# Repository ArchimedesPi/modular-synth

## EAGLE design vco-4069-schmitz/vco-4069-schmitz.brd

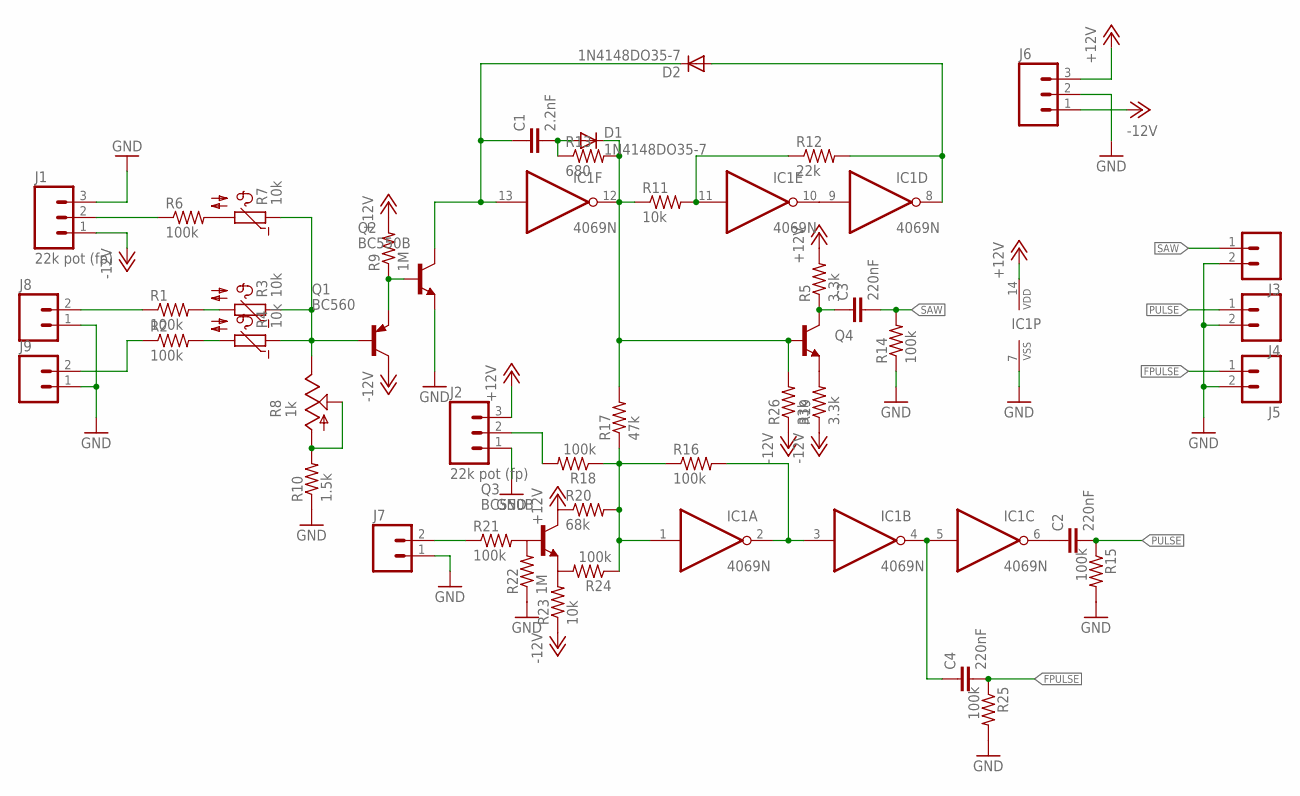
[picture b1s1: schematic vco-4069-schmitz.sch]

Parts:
C1: 2.2nF; C025-025X050
C2, C3, C4: 220nF; C025-025X050
D1, D2: 1N4148DO35-7; DO35-7
IC1: 4069N; DIL14
J1, J2: 22k pot (fp); 1X03
J3, J4, J5, J7, J8, J9: M02PTH; 1X02
J6: M03PTH; 1X03
Q1: BC560; TO92-EBC
Q2, Q3: BC550B; TO92-EBC
Q4: TRANSISTOR_NPNBC547; TO-92-AMMO
R1, R2, R6, R14, R15, R16, R18, R21, R24, R25: 100k; 0207/2V
R3, R4, R7: 10k; N640
R5, R19: 3.3k; 0207/2V
R8: 1k; B25P
R9, R22: 1M; 0207/2V
R10: 1.5k; 0207/2V
R11: 10k; 0207/2V
R12: 22k; 0207/2V
R13: 680; 0204/7
R17: 47k; 0207/2V
R20: 68k; 0207/2V
R23: 10k; 0207/5V
R26: 33k; 0207/2V

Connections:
+12V: IC1.14 (VDD), J2.3, J6.3, Q3.C, R5.2, R9.2, R20.1
-12V: J1.1, J6.1, Q1.C, R19.1, R23.1, R26.1
CV2: J9.2, R2.1
FPULSE: C4.2, J5.1, R25.1
GND: IC1.7 (VSS), J1.3, J2.1, J3.2, J4.2, J5.2, J6.2, J7.1, J8.1, J9.1, Q2.E, R10.1, R14.1, R15.2, R22.1, R25.2
unnamed: J1.2, R6.1
unnamed: R1.2, R3.2
unnamed: R6.2, R7.2
unnamed: R2.2, R4.2
unnamed: Q3.E, R23.2, R24.2
unnamed: Q1.E, Q2.B, R9.1
unnamed: R8.A, R8.S, R10.2
unnamed: C1.1, D2.C, IC1.13 (I), Q2.C
unnamed: IC1.2 (O), IC1.3 (I), R16.2
unnamed: IC1.11 (I), R11.2, R12.1
unnamed: IC1.9 (I), IC1.10 (O)
unnamed: D2.A, IC1.8 (O), R12.2
unnamed: C1.2, D1.A, R13.1
unnamed: Q4.3 (E), R19.2
unnamed: C4.1, IC1.4 (O), IC1.5 (I)
unnamed: C2.1, IC1.6 (O)
unnamed: IC1.1 (I), R16.1, R17.1, R18.1, R20.2, R24.1
unnamed: J2.2, R18.2
unnamed: Q3.B, R21.2, R22.2
unnamed: Q1.B, R3.1, R4.1, R7.1, R8.E
unnamed: J7.2, R21.1
unnamed: J8.2, R1.1
unnamed: C3.1, Q4.1 (C), R5.1
unnamed: D1.C, IC1.12 (O), Q4.2 (B), R11.1, R13.2, R17.2, R26.2
PULSE: C2.2, J4.1, R15.1
SAW: C3.2, J3.1, R14.2

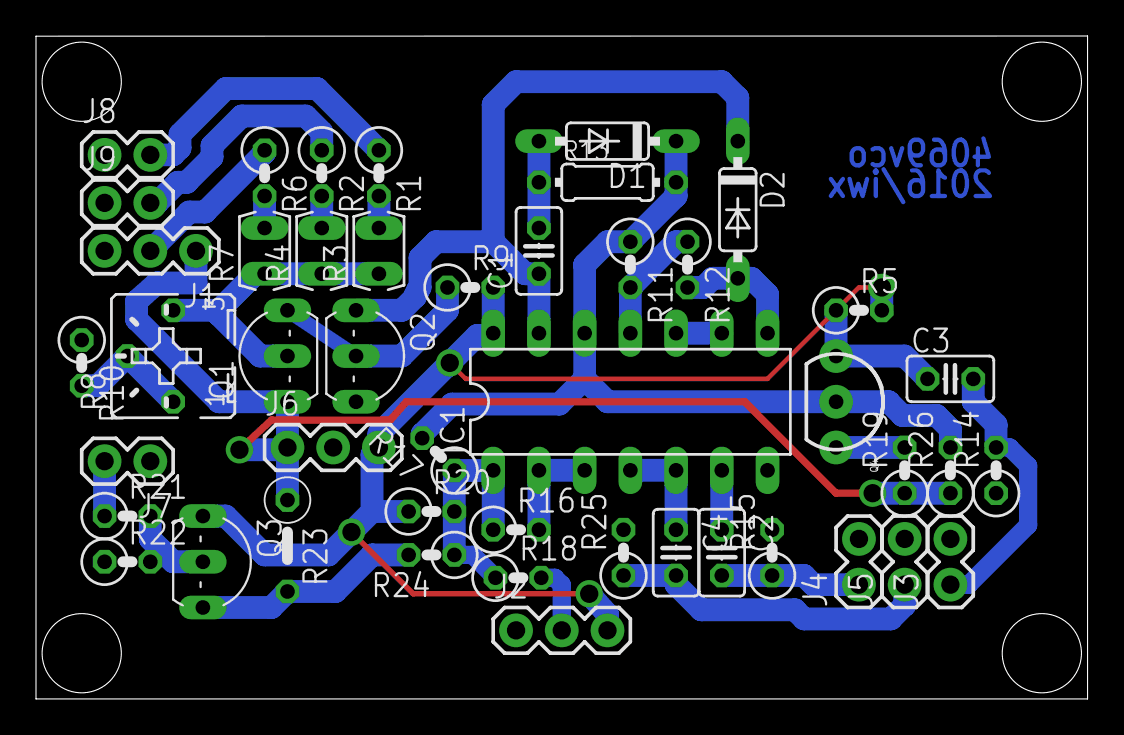
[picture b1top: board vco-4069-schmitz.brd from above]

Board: 2 copper layers, 58.4 x 36.8 mm, 46 parts (0 on the bottom side), 31 nets.

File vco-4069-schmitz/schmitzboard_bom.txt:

Partlist

Exported from vco-4069-schmitz.brd at 7/19/16 8:29 PM

EAGLE Version 7.6.0 Copyright (c) 1988-2016 CadSoft

Assembly variant: 

Part     Value          Package      Library               Position (inch)       Orientation

C1       2.2nF          C025-025X050 resistor              (1.1 0.98)            R90
C2       220nF          C025-025X050 resistor              (1.5 0.32)            R270
C3       220nF          C025-025X050 resistor              (2 0.7)               R0
C4       220nF          C025-025X050 resistor              (1.4 0.32)            R270
D1       1N4148DO35-7   DO35-7       diode                 (1.25 1.22)           R180
D2       1N4148DO35-7   DO35-7       diode                 (1.535 1.07)          R270
IC1      4069N          DIL14        40xx                  (1.3 0.65)            R0
J1       22k pot (fp)   1X03         SparkFun-Connectors   (0.35 0.98)           R180
J2       22k pot (fp)   1X03         SparkFun-Connectors   (1.05 0.15)           R0
J3                      1X02         SparkFun-Connectors   (2 0.25)              R90
J4                      1X02         SparkFun-Connectors   (1.8 0.25)            R90
J5                      1X02         SparkFun-Connectors   (1.9 0.25)            R90
J6                      1X03         SparkFun-Connectors   (0.55 0.55)           R0
J7                      1X02         SparkFun-Connectors   (0.25 0.52)           R180
J8                      1X02         SparkFun-Connectors   (0.15 1.19)           R0
J9                      1X02         SparkFun-Connectors   (0.15 1.085)          R0
Q1       BC560          TO92-EBC     transistor-pnp        (0.5 0.75)            R90
Q2       BC550B         TO92-EBC     transistor-npn        (0.75 0.75)           R270
Q3       BC550B         TO92-EBC     transistor-npn        (0.415 0.3)           R270
Q4                      TO-92-AMMO   SparkFun-DiscreteSemi (1.75 0.65)           R270
R1       100k           0207/2V      resistor              (0.75 1.15)           R270
R2       100k           0207/2V      resistor              (0.625 1.15)          R270
R3       10k            N640         ptc-ntc               (0.75 0.98)           R90
R4       10k            N640         ptc-ntc               (0.625 0.98)          R90
R5       3.3k           0207/2V      resistor              (1.8 0.85)            R0
R6       100k           0207/2V      resistor              (0.5 1.15)            R270
R7       10k            N640         ptc-ntc               (0.5 0.98)            R90
R8       1k             B25P         pot                   (0.3 0.75)            R90
R9       1M             0207/2V      resistor              (0.95 0.9)            R0
R10      1.5k           0207/2V      resistor              (0.1 0.735)           R270
R11      10k            0207/2V      resistor              (1.3 0.95)            R270
R12      22k            0207/2V      resistor              (1.425 0.95)          R270
R13      680            0204/7       resistor              (1.25 1.13)           R0
R14      100k           0207/2V      resistor              (2.1 0.5)             R90
R15      100k           0207/2V      resistor              (1.61 0.32)           R90
R16      100k           0207/2V      resistor              (1.05 0.37)           R0
R17      47k            0207/2V      resistor              (0.88 0.535)          R135
R18      100k           0207/2V      resistor              (1.055 0.265)         R0
R19      3.3k           0207/2V      resistor              (1.9 0.5)             R90
R20      68k            0207/2V      resistor              (0.865 0.41)          R0
R21      100k           0207/2V      resistor              (0.2 0.4)             R0
R22      1M             0207/2V      resistor              (0.2 0.3)             R0
R23      10k            0207/5V      resistor              (0.55 0.335)          R270
R24      100k           0207/2V      resistor              (0.865 0.315)         R180
R25      100k           0207/2V      resistor              (1.285 0.32)          R90
R26      33k            0207/2V      resistor              (2 0.5)               R90

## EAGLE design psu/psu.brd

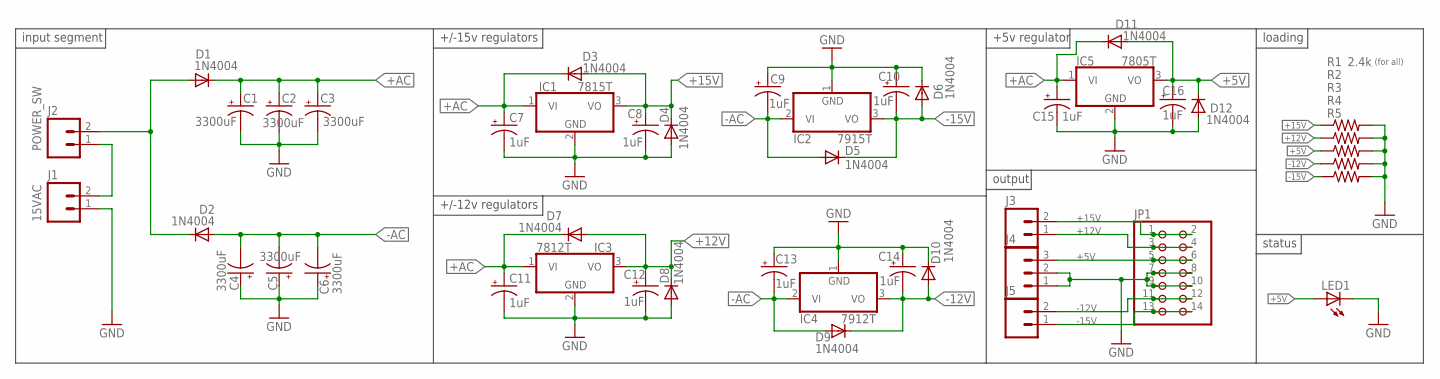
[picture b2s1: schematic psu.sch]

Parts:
C1, C2, C3, C4, C5, C6: 3300uF; E7,5-18
C7, C8, C9, C10, C11, C12, C13, C14, C15, C16: 1uF; E2,5-5
D1, D2, D3, D4, D5, D6, D7, D8, D9, D10, D11, D12: 1N4004; DO41-10
IC1: 7815T; TO220H
IC2: 7915T; TO220H
IC3: 7812T; TO220H
IC4: 7912T; TO220H
IC5: 7805T; TO220H
J1: 15VAC; SCREWTERMINAL-5MM-2
J2: POWER_SW; SCREWTERMINAL-5MM-2
J3, J5: M025MM; SCREWTERMINAL-5MM-2
J4: M03-SCREW-5MM; SCREWTERMINAL-5MM-3
JP1: PINHD-2X7; 2X07
LED1: LED3MM
R1, R2, R3, R4, R5: 2.4k; 0805

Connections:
+5V: C16.+, D11.A, D12.C, IC5.3 (VO), J4.3, JP1.5, JP1.6, LED1.A, R3.1
+12V: C12.+, D7.A, D8.C, IC3.3 (VO), J3.1, JP1.3, JP1.4, R2.1
+15V: C8.+, D3.A, D4.C, IC1.3 (VO), J3.2, JP1.1, JP1.2, R1.1
+AC: C1.+, C2.+, C3.+, C7.+, C11.+, C15.+, D1.C, D3.C, D7.C, D11.C, IC1.1 (VI), IC3.1 (VI), IC5.1 (VI)
-12V: C14.-, D9.C, D10.A, IC4.3 (VO), J5.2, JP1.11, JP1.12, R4.1
-15V: C10.-, D5.C, D6.A, IC2.3 (VO), J5.1, JP1.13, JP1.14, R5.1
-AC: C4.-, C5.-, C6.-, C9.-, C13.-, D2.A, D5.A, D9.A, IC2.2 (VI), IC4.2 (VI)
GND: C1.-, C2.-, C3.-, C4.+, C5.+, C6.+, C7.-, C8.-, C9.+, C10.+, C11.-, C12.-, C13.+, C14.+, C15.-, C16.-, D4.A, D6.C, D8.A, D10.C, D12.A, IC1.2 (GND), IC2.1 (GND), IC3.2 (GND), IC4.1 (GND), IC5.2 (GND), J1.1, J4.1, J4.2, JP1.7, JP1.8, JP1.9, JP1.10, LED1.K (C), R1.2, R2.2, R3.2, R4.2, R5.2
unnamed: J1.2, J2.1
unnamed: D1.A, D2.C, J2.2

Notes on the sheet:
input segment
+/-15v regulators
+/-12v regulators
+5v regulator
output
loading
(for all)
status

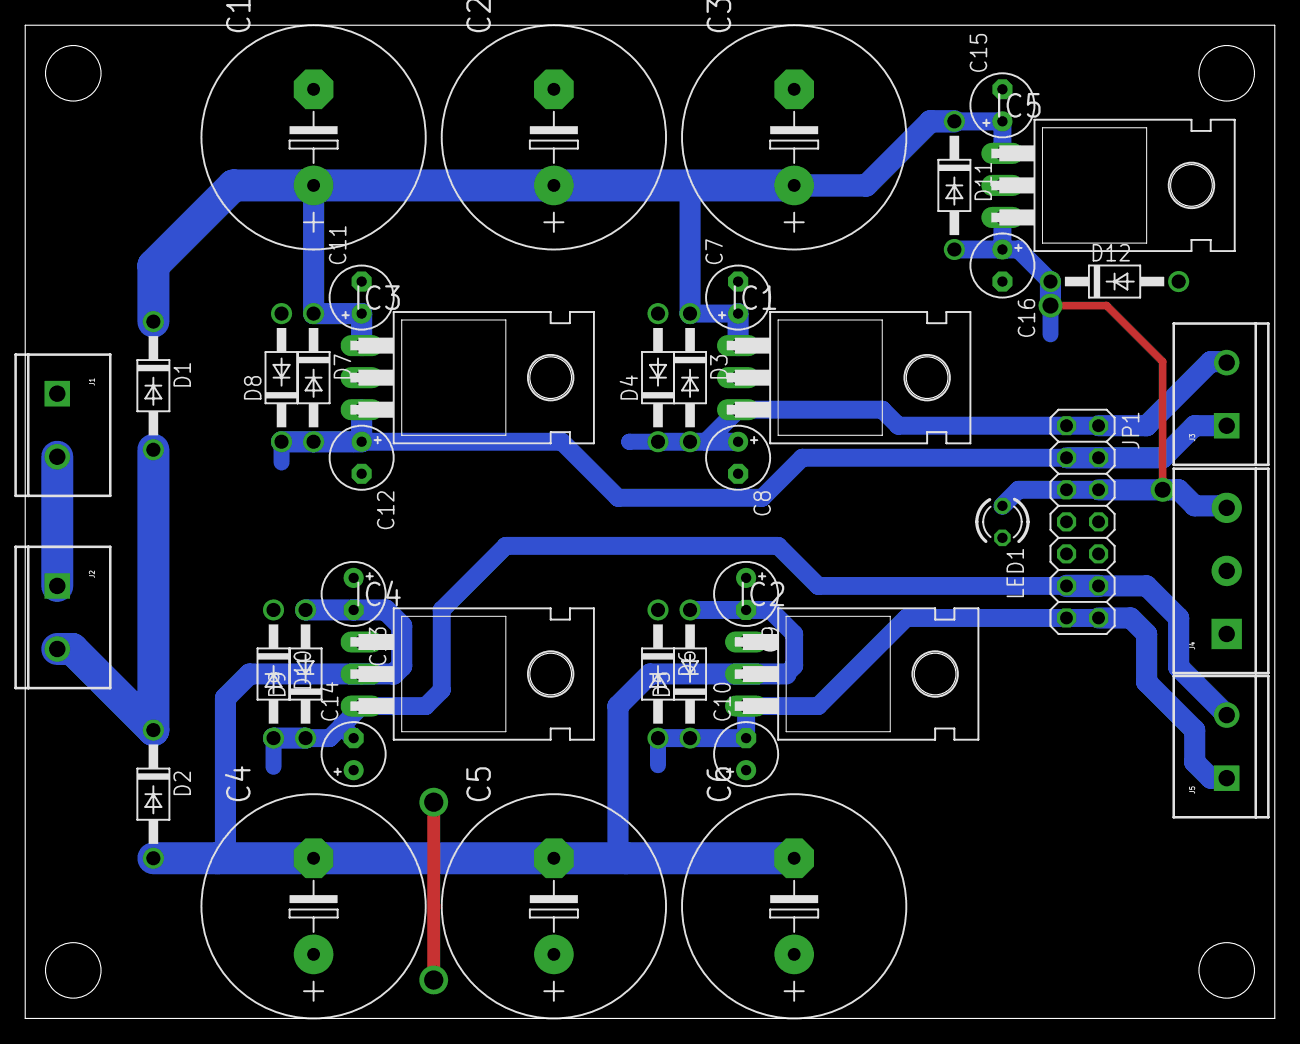
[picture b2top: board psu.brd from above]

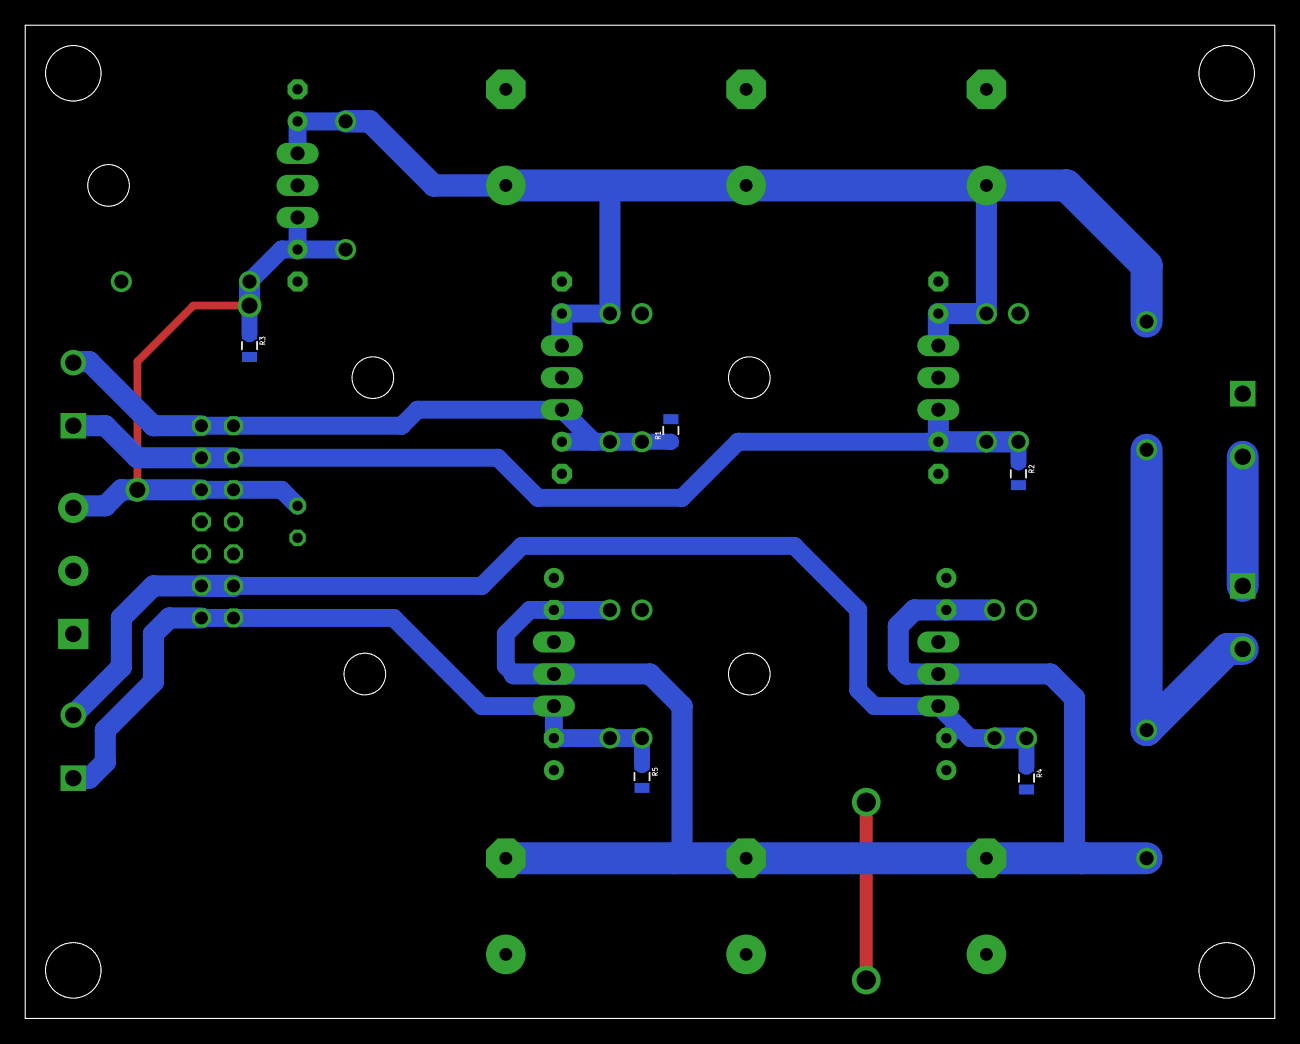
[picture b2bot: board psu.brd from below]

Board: 2 copper layers, 99.1 x 78.7 mm, 45 parts (5 on the bottom side), 10 nets.

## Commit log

2016-05-14 Add partially-finished board layouts for a power supply
2016-05-14 Finish the board layout
2016-05-14 Final version of psu, I guess?
2016-05-14 PSU board: dimensions, holes
2016-05-14 Move PSU stuff to its own folder
2016-05-14 Loading resistors for the PSU
2016-05-14 Add a eurorack panel definition for openSCAD
2016-05-15 $fn=50 for eurorack panel
2016-05-15 Schematic for a version of the 4069 Schmitz VCO
2016-05-15 Schmitz VCO board
2016-05-26 eurorack 10hp blankpanel
2016-05-26 Schmitz 4069 VCO BOM
2016-05-27 psu rev 2: fix disconnected nets, add led
2016-06-03 through-hole 4069 vco
2016-06-07 4069 vco updates
2016-07-20 bump and add board bom
2016-08-09 Add pdfs
2016-08-10 Rename

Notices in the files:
parts and their libraries:
SparkFun-Connectors: Licensing: Creative Commons ShareAlike 4.0 International - https://creativecommons.org/licenses/by-sa/4.0
